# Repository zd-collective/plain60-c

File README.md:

# Plain60-C rev2.2 (Noctus edition)

This universal 60% PCB is designed to support as little layouts as possible without limiting usability for most users. The reason I did this is because other PCBs made for this form factor usually have so many supported layouts that it could almost qualify as swiss cheese.

It also features a fuse and an ESD protection chip to protect the MCU and other parts of the PCB.

## Modifications

- modified to use the same JST header position as the WT60 by Wilba
- holes for mounting of the weight on the Noctus
- removed the usb type-c port and related hardware
- added silkscreen onto the front
- removed standard poker mounting holes
- removed speaker

## Features
- Compatible with QMK Firmware and VIA Configurator (if you flash a VIA compatible .hex file)
- JST header for connection with daughterboard
- No LEDs and no underglow
- Minimal layout support
- ISP header

## Supported layouts

## Building
If you feel like building a few of these PCBs yourself, go to the 'Releases' tab and download the latest gerber files. Order those at your favourite PCB manufacturer, get the components needed (see below) and solder them on! A hot air station is not required but a soldering iron is. Flux is recommended.

## Opening the project
To open the files you will need the latest KiCAD nightly version.

## Bill of materials (BOM)
Amount is per PCB, multiply as needed.

| LCSC part # | Description   | Value | Package  | Amount |
| ----------- | ------------- | ----- | -------- | ------:|
| C128353     | Capacitor     | 0.1uF | 0805     | 4      |
| C131056     | Capacitor     | 4.7uF | 0805     | 1      |
| C215803     | Capacitor     | 1uF   | 0805     | 1      |
| C109001     | Diode         |       | 0805     | 65     |
| C261942     | Fuse          |       | 0805     | 1      |
| C165948     | Connector     |       | SMD/THT  | 1      |
| C103904     | Resistor      | 10K   | 0805     | 2      |
| C212411     | Resistor      | 5.1K  | 0805     | 2      |
| C325772     | Resistor      | 22    | 0805     | 2      |
| C44854      | MCU           | 32U4  | QFP-44   | 1      |
| C7519       | ESD chip      |       | SOT23-6  | 1      |
| C341521     | Resonator     | 16MHz | SMD      | 1      |
| C92584      | Switch        |       | SMD      | 1      |
| C160404     | Optional JST  |       | SMD      | 1      |

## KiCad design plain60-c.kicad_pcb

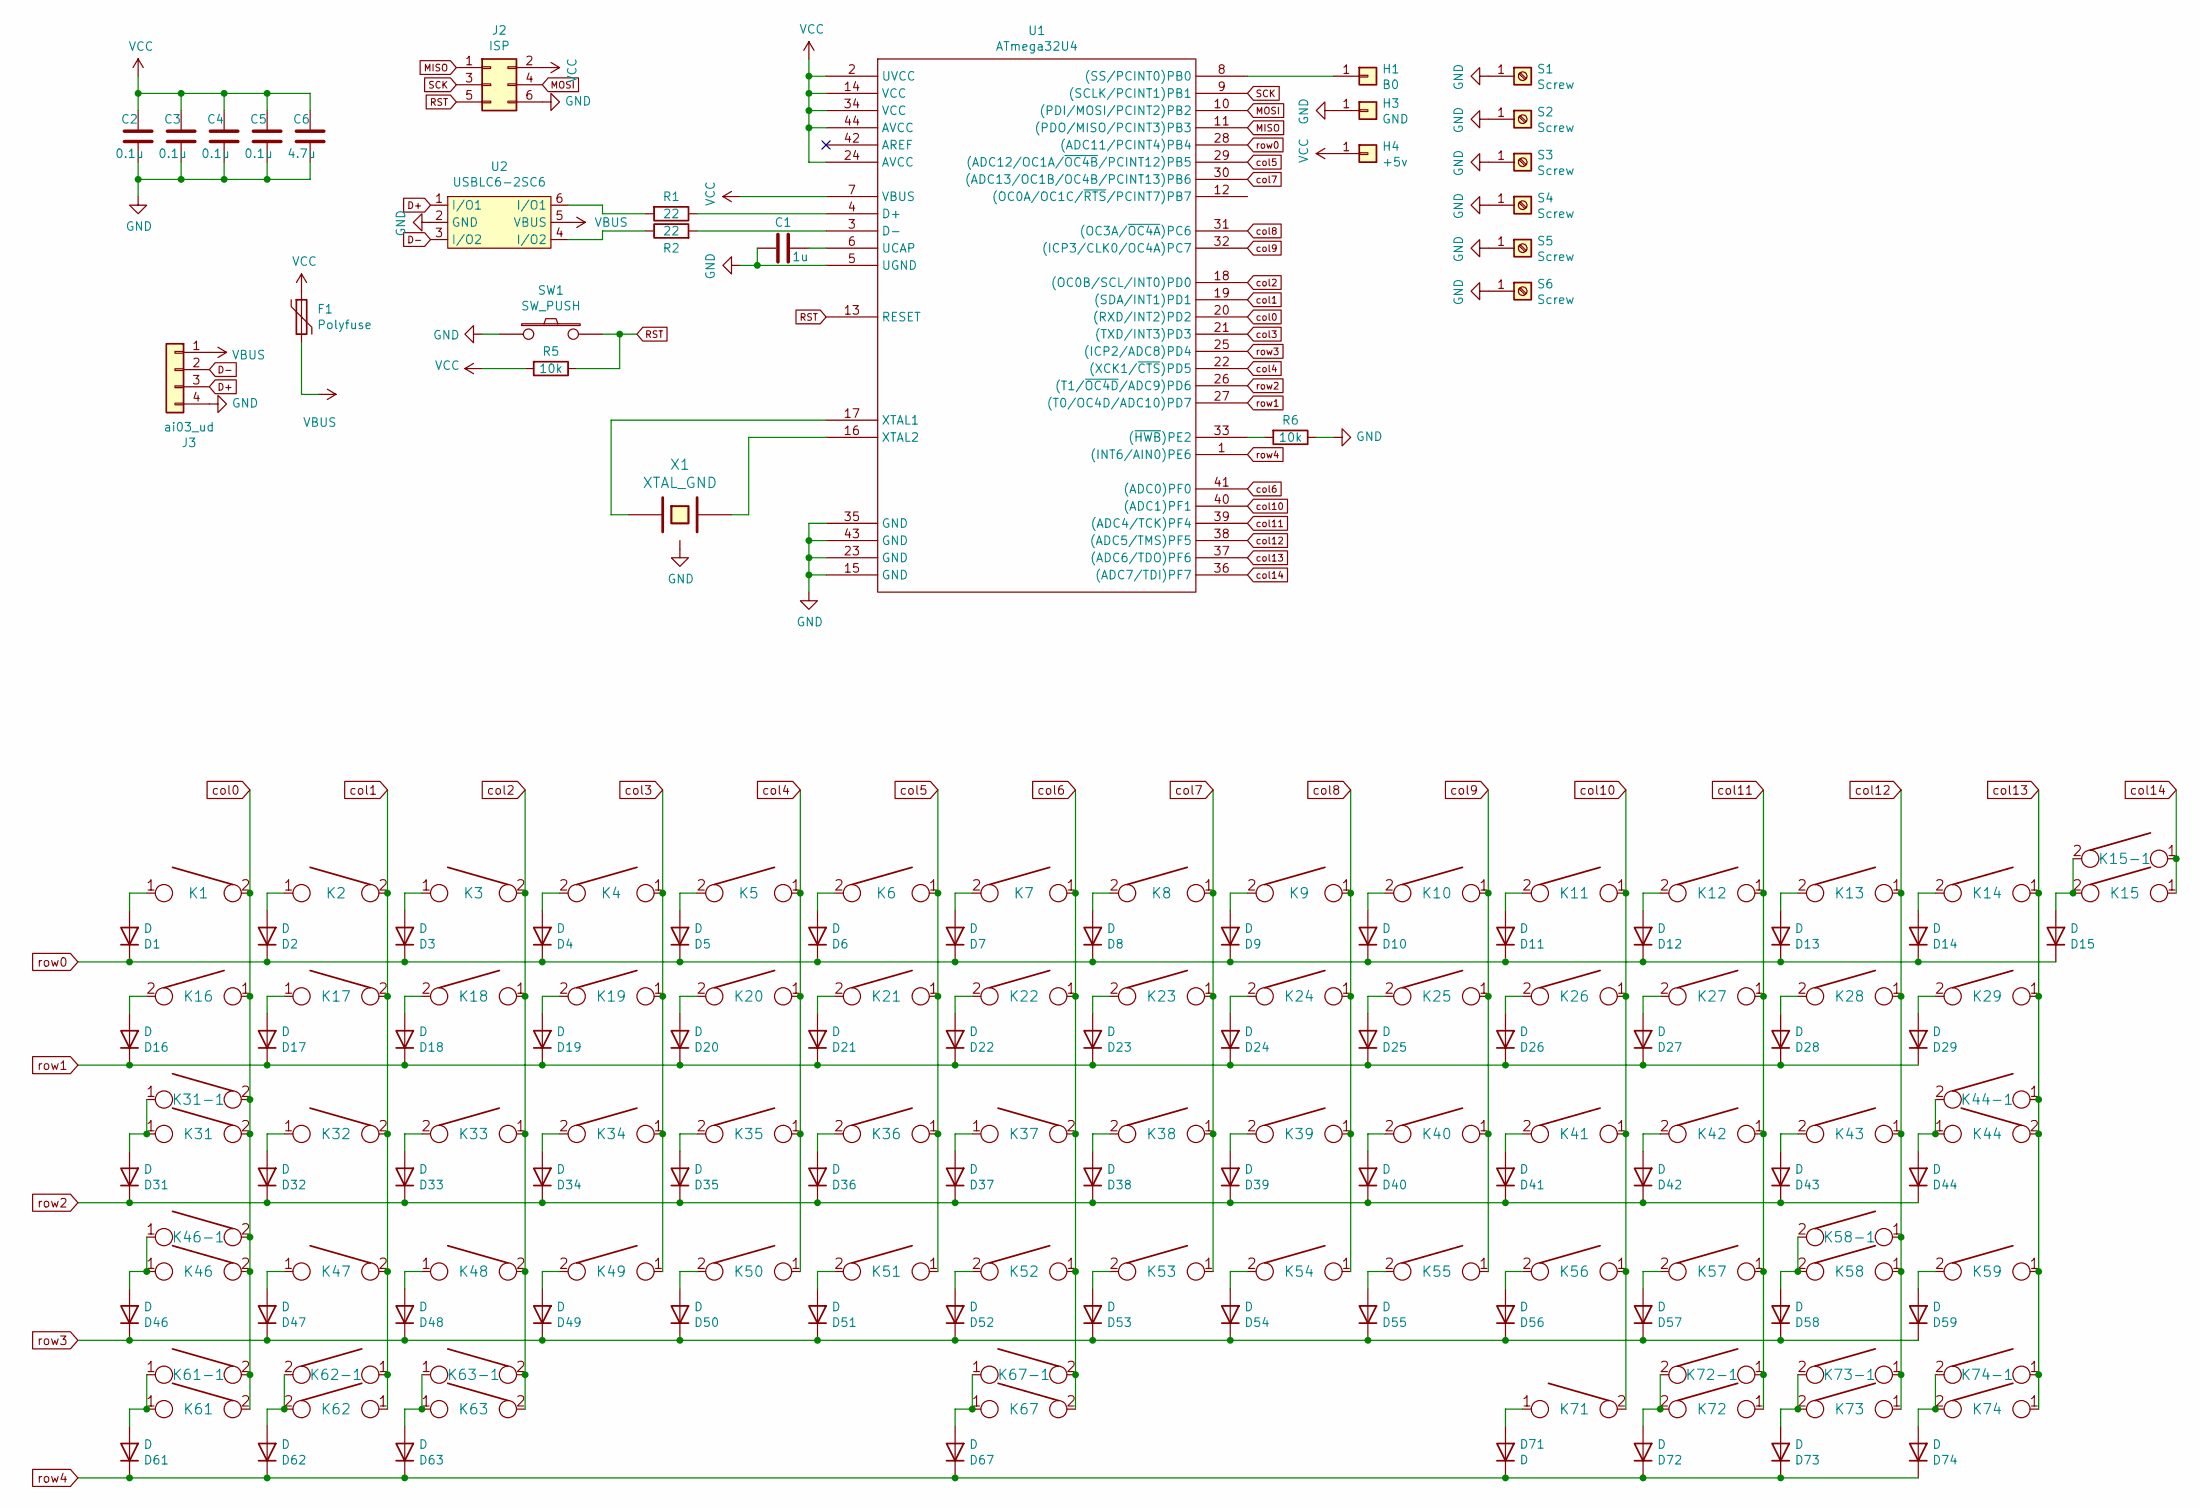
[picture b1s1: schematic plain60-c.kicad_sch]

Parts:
C1: 1u; C_0805
C2, C3, C4, C5: 0.1u; C_0805
C6: 4.7u; C_0805
D1, D2, D3, D4, D5, D6, D7, D8, D9, D10, D11, D12, D13, D14, D15, D16, D17, D18, D19, D20, D21, D22, D23, D24, D25, D26, D27, D28, D29, D31, D32, D33, D34, D35, D36, D37, D38, D39, D40, D41, D42, D43, D44, D46, D47, D48, D49, D50, D51, D52, D53, D54, D55, D56, D57, D58, D59, D61, D62, D63, D67, D71, D72, D73, D74: D; D_0805
F1: Polyfuse; R_0805
H1: B0; free_pin
H3: GND; free_pin
H4: +5v; free_pin
J2: ISP; isp_standard
J3: ai03_ud; JST_SH_SM04B-SRSS-TB_1x04-1MP_P1.00mm_Horizontal
K1, K2, K3, K4, K5, K6, K7, K8, K9, K10, K11, K12, K13, K14, K15-1, K17, K18, K19, K20, K21, K22, K23, K24, K25, K26, K27, K28, K32, K33, K34, K35, K36, K37, K38, K39, K40, K41, K42, K43, K47, K48, K49, K50, K51, K52, K53, K54, K55, K56, K57, K59, K62-1, K73-1: KEYSW; CHERRY_PLATE_100H
K15: KEYSW; CHERRY_PCB_200H
K16, K29, K61-1, K63-1, K72-1, K74-1: KEYSW; CHERRY_PLATE_150H
K31, K58-1: KEYSW; CHERRY_PLATE_175H
K31-1, K46-1, K61, K62, K63, K71, K72, K73, K74: KEYSW; CHERRY_PLATE_125H
K44, K46: KEYSW; CHERRY_PCB_225H
K44-1: KEYSW; CHERRY_PCB_200H_V
K58: KEYSW; CHERRY_PCB_275H
K67: KEYSW; CHERRY_PCB_625H_F
K67-1: KEYSW; CHERRY_PCB_700H_F
R1, R2: 22; R_0805
R5, R6: 10k; R_0805
S1, S2, S3, S6: Screw; 5.5_5x2.5mm
S4, S5: Screw; 10x5_7x2.5mm
SW1: SW_PUSH; SW_SPST_TL3342
U1: ATmega32U4; ATMEGA32U4
U2: USBLC6-2SC6; Farnell 1295310
X1: XTAL_GND; Resonator_SMD_muRata_CSTNExxV-3Pin-p1.2

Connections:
D+: J3.3, U2.1 (I/O1)
D-: J3.2, U2.3 (I/O2)
GND: C1.2, C2.1, C3.1, C4.1, C5.1, C6.1, H3.1, J2.6, J3.4, R6.1, S1.1, S2.1, S3.1, S4.1, S5.1, S6.1, SW1.1, U1.5 (UGND), U1.15 (GND), U1.23 (GND), U1.35 (GND), U1.43 (GND), U2.2 (GND), X1.3
MISO: J2.1, U1.11 ((PDO/MISO/PCINT3)PB3)
MOSI: J2.4, U1.10 ((PDI/MOSI/PCINT2)PB2)
unnamed: C1.1, U1.6 (UCAP)
unnamed: D1.2 (A), K1.1
unnamed: D2.2 (A), K2.1
unnamed: D3.2 (A), K3.1
unnamed: D4.2 (A), K4.2
unnamed: D5.2 (A), K5.2
unnamed: D6.2 (A), K6.2
unnamed: D7.2 (A), K7.2
unnamed: D8.2 (A), K8.2
unnamed: D9.2 (A), K9.2
unnamed: D10.2 (A), K10.2
unnamed: D11.2 (A), K11.2
unnamed: D12.2 (A), K12.2
unnamed: D13.2 (A), K13.2
unnamed: D14.2 (A), K14.2
unnamed: D15.2 (A), K15.2, K15-1.2
unnamed: D16.2 (A), K16.2
unnamed: D17.2 (A), K17.1
unnamed: D18.2 (A), K18.2
unnamed: D19.2 (A), K19.2
unnamed: D20.2 (A), K20.2
unnamed: D21.2 (A), K21.2
unnamed: D22.2 (A), K22.2
unnamed: D23.2 (A), K23.2
unnamed: D24.2 (A), K24.2
unnamed: D25.2 (A), K25.2
unnamed: D26.2 (A), K26.2
unnamed: D27.2 (A), K27.2
unnamed: D28.2 (A), K28.2
unnamed: D29.2 (A), K29.2
unnamed: D31.2 (A), K31.1, K31-1.1
unnamed: D32.2 (A), K32.1
unnamed: D33.2 (A), K33.2
unnamed: D34.2 (A), K34.2
unnamed: D35.2 (A), K35.2
unnamed: D36.2 (A), K36.2
unnamed: D37.2 (A), K37.1
unnamed: D38.2 (A), K38.2
unnamed: D39.2 (A), K39.2
unnamed: D40.2 (A), K40.2
unnamed: D41.2 (A), K41.2
unnamed: D42.2 (A), K42.2
unnamed: D43.2 (A), K43.2
unnamed: D44.2 (A), K44.1, K44-1.2
unnamed: D46.2 (A), K46.1, K46-1.1
unnamed: D47.2 (A), K47.1
unnamed: D48.2 (A), K48.1
unnamed: D49.2 (A), K49.2
unnamed: D50.2 (A), K50.2
unnamed: D51.2 (A), K51.2
unnamed: D52.2 (A), K52.2
unnamed: D53.2 (A), K53.2
unnamed: D54.2 (A), K54.2
unnamed: D55.2 (A), K55.2
unnamed: D56.2 (A), K56.2
unnamed: D57.2 (A), K57.2
unnamed: D58.2 (A), K58.2, K58-1.2
unnamed: D59.2 (A), K59.2
unnamed: D61.2 (A), K61.1, K61-1.1
unnamed: D62.2 (A), K62.2, K62-1.2
unnamed: D63.2 (A), K63.1, K63-1.1
unnamed: D67.2 (A), K67.1, K67-1.1
unnamed: D71.2 (A), K71.1
unnamed: D72.2 (A), K72.2, K72-1.2
unnamed: D73.2 (A), K73.2, K73-1.2
unnamed: D74.2 (A), K74.2, K74-1.2
unnamed: H1.1, U1.8 ((SS/PCINT0)PB0)
unnamed: R1.1, U1.4 (D+)
unnamed: R1.2, U2.6 (I/O1)
unnamed: R2.1, U2.4 (I/O2)
unnamed: R2.2, U1.3 (D-)
unnamed: R6.2, U1.33 ((~HWB~)PE2)
unnamed: U1.16 (XTAL2), X1.2
unnamed: U1.17 (XTAL1), X1.1
RST: J2.5, R5.1, SW1.2, U1.13 (RESET)
SCK: J2.3, U1.9 ((SCLK/PCINT1)PB1)
VBUS: F1.2, J3.1, U2.5 (VBUS)
VCC: C2.2, C3.2, C4.2, C5.2, C6.2, F1.1, H4.1, J2.2, R5.2, U1.2 (UVCC), U1.7 (VBUS), U1.14 (VCC), U1.24 (AVCC), U1.34 (VCC), U1.44 (AVCC)
col0: K1.2, K16.1, K31.2, K31-1.2, K46.2, K46-1.2, K61.2, K61-1.2, U1.20 ((RXD/INT2)PD2)
col1: K2.2, K17.2, K32.2, K47.2, K62.1, K62-1.1, U1.19 ((SDA/INT1)PD1)
col2: K3.2, K18.1, K33.1, K48.2, K63.2, K63-1.2, U1.18 ((OC0B/SCL/INT0)PD0)
col3: K4.1, K19.1, K34.1, K49.1, U1.21 ((TXD/INT3)PD3)
col4: K5.1, K20.1, K35.1, K50.1, U1.22 ((XCK1/~CTS~)PD5)
col5: K6.1, K21.1, K36.1, K51.1, U1.29 ((ADC12/OC1A/~OC4B~/PCINT12)PB5)
col6: K7.1, K22.1, K37.2, K52.1, K67.2, K67-1.2, U1.41 ((ADC0)PF0)
col7: K8.1, K23.1, K38.1, K53.1, U1.30 ((ADC13/OC1B/OC4B/PCINT13)PB6)
col8: K9.1, K24.1, K39.1, K54.1, U1.31 ((OC3A/~OC4A~)PC6)
col9: K10.1, K25.1, K40.1, K55.1, U1.32 ((ICP3/CLK0/OC4A)PC7)
col10: K11.1, K26.1, K41.1, K56.1, K71.2, U1.40 ((ADC1)PF1)
col11: K12.1, K27.1, K42.1, K57.1, K72.1, K72-1.1, U1.39 ((ADC4/TCK)PF4)
col12: K13.1, K28.1, K43.1, K58.1, K58-1.1, K73.1, K73-1.1, U1.38 ((ADC5/TMS)PF5)
col13: K14.1, K29.1, K44.2, K44-1.1, K59.1, K74.1, K74-1.1, U1.37 ((ADC6/TDO)PF6)
col14: K15.1, K15-1.1, U1.36 ((ADC7/TDI)PF7)
row0: D1.1 (K), D2.1 (K), D3.1 (K), D4.1 (K), D5.1 (K), D6.1 (K), D7.1 (K), D8.1 (K), D9.1 (K), D10.1 (K), D11.1 (K), D12.1 (K), D13.1 (K), D14.1 (K), D15.1 (K), U1.28 ((ADC11/PCINT4)PB4)
row1: D16.1 (K), D17.1 (K), D18.1 (K), D19.1 (K), D20.1 (K), D21.1 (K), D22.1 (K), D23.1 (K), D24.1 (K), D25.1 (K), D26.1 (K), D27.1 (K), D28.1 (K), D29.1 (K), U1.27 ((T0/OC4D/ADC10)PD7)
row2: D31.1 (K), D32.1 (K), D33.1 (K), D34.1 (K), D35.1 (K), D36.1 (K), D37.1 (K), D38.1 (K), D39.1 (K), D40.1 (K), D41.1 (K), D42.1 (K), D43.1 (K), D44.1 (K), U1.26 ((T1/~OC4D~/ADC9)PD6)
row3: D46.1 (K), D47.1 (K), D48.1 (K), D49.1 (K), D50.1 (K), D51.1 (K), D52.1 (K), D53.1 (K), D54.1 (K), D55.1 (K), D56.1 (K), D57.1 (K), D58.1 (K), D59.1 (K), U1.25 ((ICP2/ADC8)PD4)
row4: D61.1 (K), D62.1 (K), D63.1 (K), D67.1 (K), D71.1 (K), D72.1 (K), D73.1 (K), D74.1 (K), U1.1 ((INT6/AIN0)PE6)

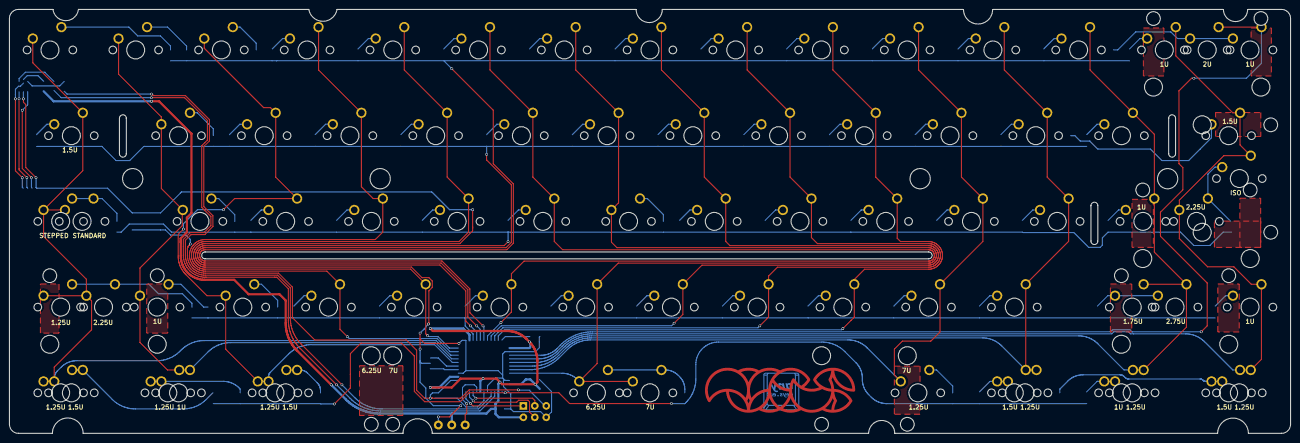
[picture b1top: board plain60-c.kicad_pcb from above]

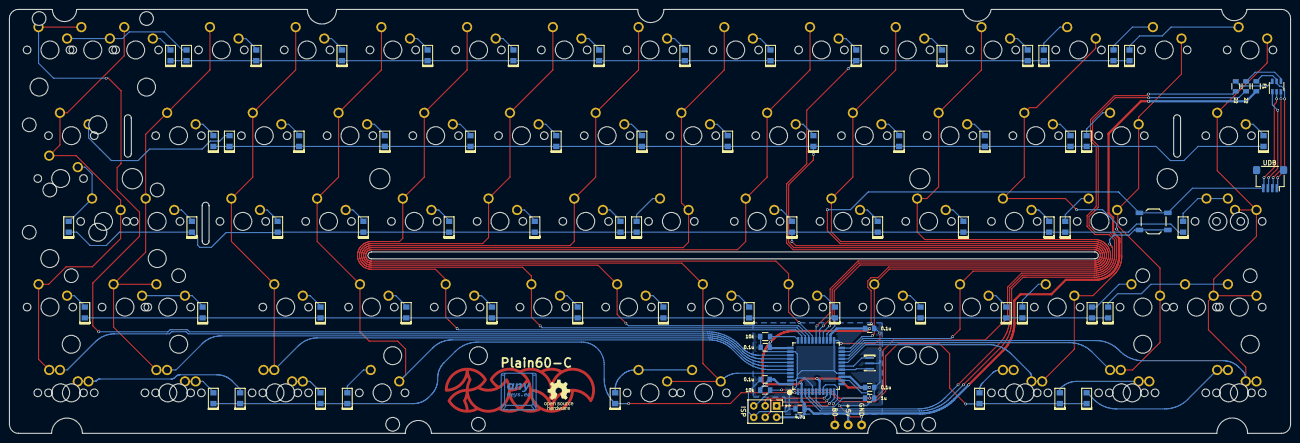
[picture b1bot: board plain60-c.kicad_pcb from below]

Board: 2 copper layers, 284.7 x 94.2 mm, 162 parts (85 on the bottom side), 103 nets.

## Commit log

2020-10-30 add holes and move jst position
2020-10-31 readme updated also added holes and shit
2020-11-06 remove usb-c and add back silkscreen
2020-11-06 changed silk, removed poker mounts
2020-11-09 rounded traces and updated gerbers
2020-11-17 add soldermask and fix trace
2020-11-18 fixed some traces and redo gerber
2020-12-10 add side cuts
2020-12-18 edited traces
2020-12-18 add cut
2020-12-18 fix thing
2020-12-30 pain
